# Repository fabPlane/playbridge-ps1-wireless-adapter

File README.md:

# PlayBridge PS1 Wireless Adapter

PlayBridge is an ESP32-based wireless bridge that receives PC controller state
over Wi-Fi and presents it to an original PlayStation through the native PS1
controller protocol.

## Hardware versions

| Version | Design | Status |
| --- | --- | --- |
| `v1.0.0` | Direct PCB-mounted PS1 pin array | Frozen prototype checkpoint under [`versions/v1-pcb-mounted-pin-array/`](versions/v1-pcb-mounted-pin-array/) |
| `v2.0.0` | Modular donor-plug harness through board-mounted 9-contact connectors | Frozen release candidate under [`versions/v2-donor-plug-modular-adapter/`](versions/v2-donor-plug-modular-adapter/) |
| `v2.1.0` | V2.0 baseline plus status LEDs and UART debug access | Release candidate under [`versions/v2.1-status-leds-uart-debug/`](versions/v2.1-status-leds-uart-debug/) |
| `v3.0.0` | Combined PS1 controller and serial-harness evaluation | Frozen development checkpoint under [`versions/v3.0-ps1-serial-harness/`](versions/v3.0-ps1-serial-harness/) |
| `v4.0.0` | New two-layer controller/serial bridge with protected dual-source power | Digitally verified design under [`versions/v4.0-controller-serial-bridge/`](versions/v4.0-controller-serial-bridge/); physical qualification pending |
| `v4.1.0` | V4.0 electrical design with ANTS-compatible enlarged routed vias | Digitally verified fabrication revision under [`versions/v4.1-controller-serial-bridge/`](versions/v4.1-controller-serial-bridge/); physical qualification pending |

Each hardware version is a self-contained FabDesk project under `versions/`.
Open the version directory itself in FabDesk; the repository root is only the
project index plus shared firmware and documentation.

## V4.0.0 status

- Board: 68 × 60 mm, two copper layers.
- J1: PS1 controller harness with open-drain DATA and ACK stages.
- J2: PS1 serial harness on ESP32 UART2.
- Power: protected USB-C and PS1 inputs, TPS2116 source mux, AP63203 buck,
  and AP2112K 3.3 V regulation.
- Programming: CH340C with manual BOOT and RESET switches; automatic DTR/RTS
  behavior is present but is not required for acceptance.
- Indicators: always-on power LED and firmware-controlled status LED.
- Digital checks: ERC, DRC, schematic/PCB parity, BOM/CPL reference parity,
  fabrication archive integrity, and export manifest all pass.
- Manufacturing: bare-board Gerbers and in-house assembly BOM/CPL are present.
- Production remains on hold until the current-limited power, source-switching,
  programming, J1, and J2 bench tests are recorded.

See [`versions/v4.0-controller-serial-bridge/README.md`](versions/v4.0-controller-serial-bridge/README.md)
for the design summary and exact connector/GPIO maps.

## V4.1.0 fabrication revision

V4.1 preserves the V4.0 schematic, component placement, connector mechanics,
GPIO map, and BOM. Its routed through-vias are enlarged to 0.90 mm copper
diameter with 0.40 mm drills to satisfy the ANTS PCB production feedback.
The affected escape routing and manufacturing outputs were regenerated and
pass ERC, DRC, connectivity, drill, and archive-integrity checks. The same
physical bench-test hold still applies.

## V3.0 and V4.0 comparison

| Area | V3.0 | V4.0 | Compatibility / action |
| --- | --- | --- | --- |
| J1/J2 | Hong Cheng C7501856; same signal pinout | Same | Harness-compatible |
| Shells | Isolated | J1→GND pad 4; J2→GND pad 7 | Grounding changed |
| Placement | J1 `(8.025,50.825)`; J2 `(26.025,50.825)` mm | J1 `(14,48.5)`; J2 `(39.2,48.5)` mm | Not mechanically drop-in |
| Controller GPIO | CMD32, CLK33, ATT34, DATA19, ACK21 | CMD19, CLK32, ATT21, DATA33, ACK27/sense34 | Firmware change |
| DATA/ACK | 2N7002 open-drain; no ACK sense | Same drivers plus ACK sense | Firmware change |
| J2 UART | TX17 / RX16 | TX17 / RX16 | Compatible |
| Power | AP63203 + AP2112K + TPS2113A | AP63203 + AP2112K + TPS2116 | Mux changed |
| Protection | USBLC6, SMBJ12A, BAT54 clamps | SMAJ TVS, TPD2EUSB30A, ACK ESD | Prototype-test required |
| LEDs | Red power; yellow-green status GPIO4 | Green power; blue status GPIO25 | GPIO/color change |
| Programming | CH340C; manual BOOT/RESET; DTR/RTS | Same | Auto mode unqualified |
| PCB | 56.295 × 62 mm; 4-layer; 1.2 mm | 68 × 60 mm; 2-layer; 1.6 mm | Size/stackup changed |
| Validation | J1/J2 PoC tested | Digital checks pass; bench pending | First prototype only |

## V2.0.0 historical status

_Board render created with [PCB Fiddle](https://pcbfiddle.com/)._

- Board: 56.295 × 62.000 mm, four copper layers, 1.20 mm thick.
- J1: 9-contact non-USB connector for a genuine PS1 donor-plug harness.
- J2: mechanically identical reserved connector; every contact is intentionally NC.
- J3: USB-C programming/power receptacle on the right edge, facing outward.
- J1 and J2: lower-edge mating mouths face outward and remain registered to the approved Molex footprints.
- Routing: complete; zero unconnected items.
- DRC: zero errors and zero warnings.
- ERC: zero errors and zero warnings.
- Schematic/PCB parity: zero findings.
- FabDesk release gate: PASS.
- PCBA data: 63 fitted references, 32 grouped BOM lines, and four DNP test pads.
- Controller-port bench firmware passed visible original-PS1 system-menu testing over Wi-Fi: all supported digital buttons worked, quick clicks were reliable, and the final check recorded 17,913 complete polls.

The design release is electrically and mechanically validated. Ordering still
requires a final live JLCPCB stock check and review of the uploaded BOM/CPL
rotation previews; see
[`versions/v2-donor-plug-modular-adapter/ordering/DO-NOT-ORDER.md`](versions/v2-donor-plug-modular-adapter/ordering/DO-NOT-ORDER.md).

## Repository layout

- `versions/v1-pcb-mounted-pin-array/` — complete frozen V1 FabDesk project, fit checks, historical renders, and provisional-contact studies.
- `versions/v2-donor-plug-modular-adapter/` — complete V2.0.0 FabDesk project, manufacturing package, reports, tools, references, and accepted renders.
- `versions/v2.1-status-leds-uart-debug/` — complete V2.1.0 FabDesk project, debug interface, manufacturing package, reports, tools, and accepted renders.
- `versions/v3.0-ps1-serial-harness/` — complete V3.0 controller/serial-harness development checkpoint and PoC evidence.
- `versions/v4.0-controller-serial-bridge/` — complete V4.0 FabDesk project, local libraries, validation evidence, renders, and manufacturing package.
- `versions/v4.1-controller-serial-bridge/` — V4.1 ANTS-compatible via revision, regenerated validation evidence, renders, and manufacturing package.
- `firmware/playbridge_wifi_test/` — shared ESP32 Wi-Fi controller firmware and bench instructions.
- `docs/` — shared protocol and modular-interconnect diagrams.

## Opening a hardware project

In FabDesk, select the desired directory under `versions/`, not the repository
root. New hardware work should begin by copying the latest applicable version
to a new version directory so previous releases remain unchanged.

## Important connector warning

J1 and J2 use USB 3 Type-A connector hardware only as inexpensive keyed
9-contact interconnects. They carry native console signals and are **NOT USB**.
Never connect either port to a computer, charger, or ordinary USB peripheral.

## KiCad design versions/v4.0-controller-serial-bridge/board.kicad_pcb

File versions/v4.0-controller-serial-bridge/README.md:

# PlayBridge V4.0 — controller + serial bridge

Status: **digital verification PASS; production HOLD pending physical bench tests**.

V4.0 is the self-contained FabDesk/KiCad project for the 68 × 60 mm,
two-layer PlayBridge board. It combines the PS1 controller interface on J1,
the PS1 serial interface on J2, USB-C programming/power, protected PS1 power,
and automatic source selection.

## Interfaces

- J1: pin 1 NC, 2 CMD, 3 CLK, 4 GND, 5 ATT, 6 DATA, 7 ACK, 8 PS1 power,
  and 9 NC. Both shell/retention pads are GND through pad 4.
- J2: pin 1 TX, 4 RX, and 7 GND; all other signal pins are NC. Both
  shell/retention pads are GND through pad 7.
- J1 and J2 use USB-A connector hardware only as keyed PS1 harness ports.
  They are **NOT USB**.
- The SERVICE / DEBUG holes are GND, UART0 TX, and UART0 RX at 3.2 mm pitch.

The exact firmware GPIO map is in `exports/firmware-handoff.md` and
`exports/firmware-pin-map.h`.

## V3.0 and V4.0 comparison

| Area | V3.0 | V4.0 | Compatibility / action |
| --- | --- | --- | --- |
| J1/J2 | Hong Cheng C7501856; same signal pinout | Same | Harness-compatible |
| Shells | Isolated | J1→GND pad 4; J2→GND pad 7 | Grounding changed |
| Placement | J1 `(8.025,50.825)`; J2 `(26.025,50.825)` mm | J1 `(14,48.5)`; J2 `(39.2,48.5)` mm | Not mechanically drop-in |
| Controller GPIO | CMD32, CLK33, ATT34, DATA19, ACK21 | CMD19, CLK32, ATT21, DATA33, ACK27/sense34 | Firmware change |
| DATA/ACK | 2N7002 open-drain; no ACK sense | Same drivers plus ACK sense | Firmware change |
| J2 UART | TX17 / RX16 | TX17 / RX16 | Compatible |
| Power | AP63203 + AP2112K + TPS2113A | AP63203 + AP2112K + TPS2116 | Mux changed |
| Protection | USBLC6, SMBJ12A, BAT54 clamps | SMAJ TVS, TPD2EUSB30A, ACK ESD | Prototype-test required |
| LEDs | Red power; yellow-green status GPIO4 | Green power; blue status GPIO25 | GPIO/color change |
| Programming | CH340C; manual BOOT/RESET; DTR/RTS | Same | Auto mode unqualified |
| PCB | 56.295 × 62 mm; 4-layer; 1.2 mm | 68 × 60 mm; 2-layer; 1.6 mm | Size/stackup changed |
| Validation | J1/J2 PoC tested | Digital checks pass; bench pending | First prototype only |

## Electrical and mechanical verification evidence

- ERC: 0 errors and 0 warnings.
- DRC: 0 violations, 0 unconnected pads, and 0 schematic-parity issues.
- Connectivity: 53/53 named nets and 227/227 connected nodes match.
- Board: 68 × 60 mm, two copper layers.
- J1/J2 signal pins and retention legs cross the 1.6 mm PCB and protrude
  about 1.2 mm below it for soldering.
- Every fitted footprint has a 3D model; TP1/TP2/TP3 are intentionally DNP.
- Engineering BOM: 80 references. Assembly BOM/CPL: 77 fitted references,
  with an exact reference-set match and no blank LCSC codes.
- The fabrication ZIP contains the complete Gerber and drill set and passes
  archive integrity testing.
- `exports/manifest-sha256.txt` verifies the canonical project, manufacturing
  outputs, accepted renders, and final reports.

## Directory layout

- `board.kicad_*`, `circuit.netlist.json`, and `fabdesk.json` — canonical project.
- `NewPlayBridge.pretty/`, `NewPlayBridge.kicad_sym`, and
  `PlayBridge.3dshapes/` — project-local libraries and models.
- `exports/` — canonical Gerbers, fabrication ZIP, BOM, CPL, positions,
  shopping list, firmware handoff, interchange files, and checksum manifest.
- `ordering/` — convenient vendor-facing copies for bare-board ordering and
  in-house assembly preparation.
- `reports/` — final electrical, mechanical, procurement, and verification evidence.
- `renders/` — generated populated-board, connector, and GLB renders.

Open this version directory itself in FabDesk; do not open the repository root.

## Bench-test hold

No assembled V4 board has been bench-qualified. Complete and record the plan
in `reports/bench-test.md` before production approval. In particular, verify
current-limited USB and PS1 power, TPS2116 source switching and backfeed,
manual programming, J1 controller waveforms, J2 UART operation, and L1
temperature/current margin. Manual BOOT/RESET is the accepted programming path.

See `RELEASE-v4.0.0.md` for the digitally verified design-checkpoint statement.

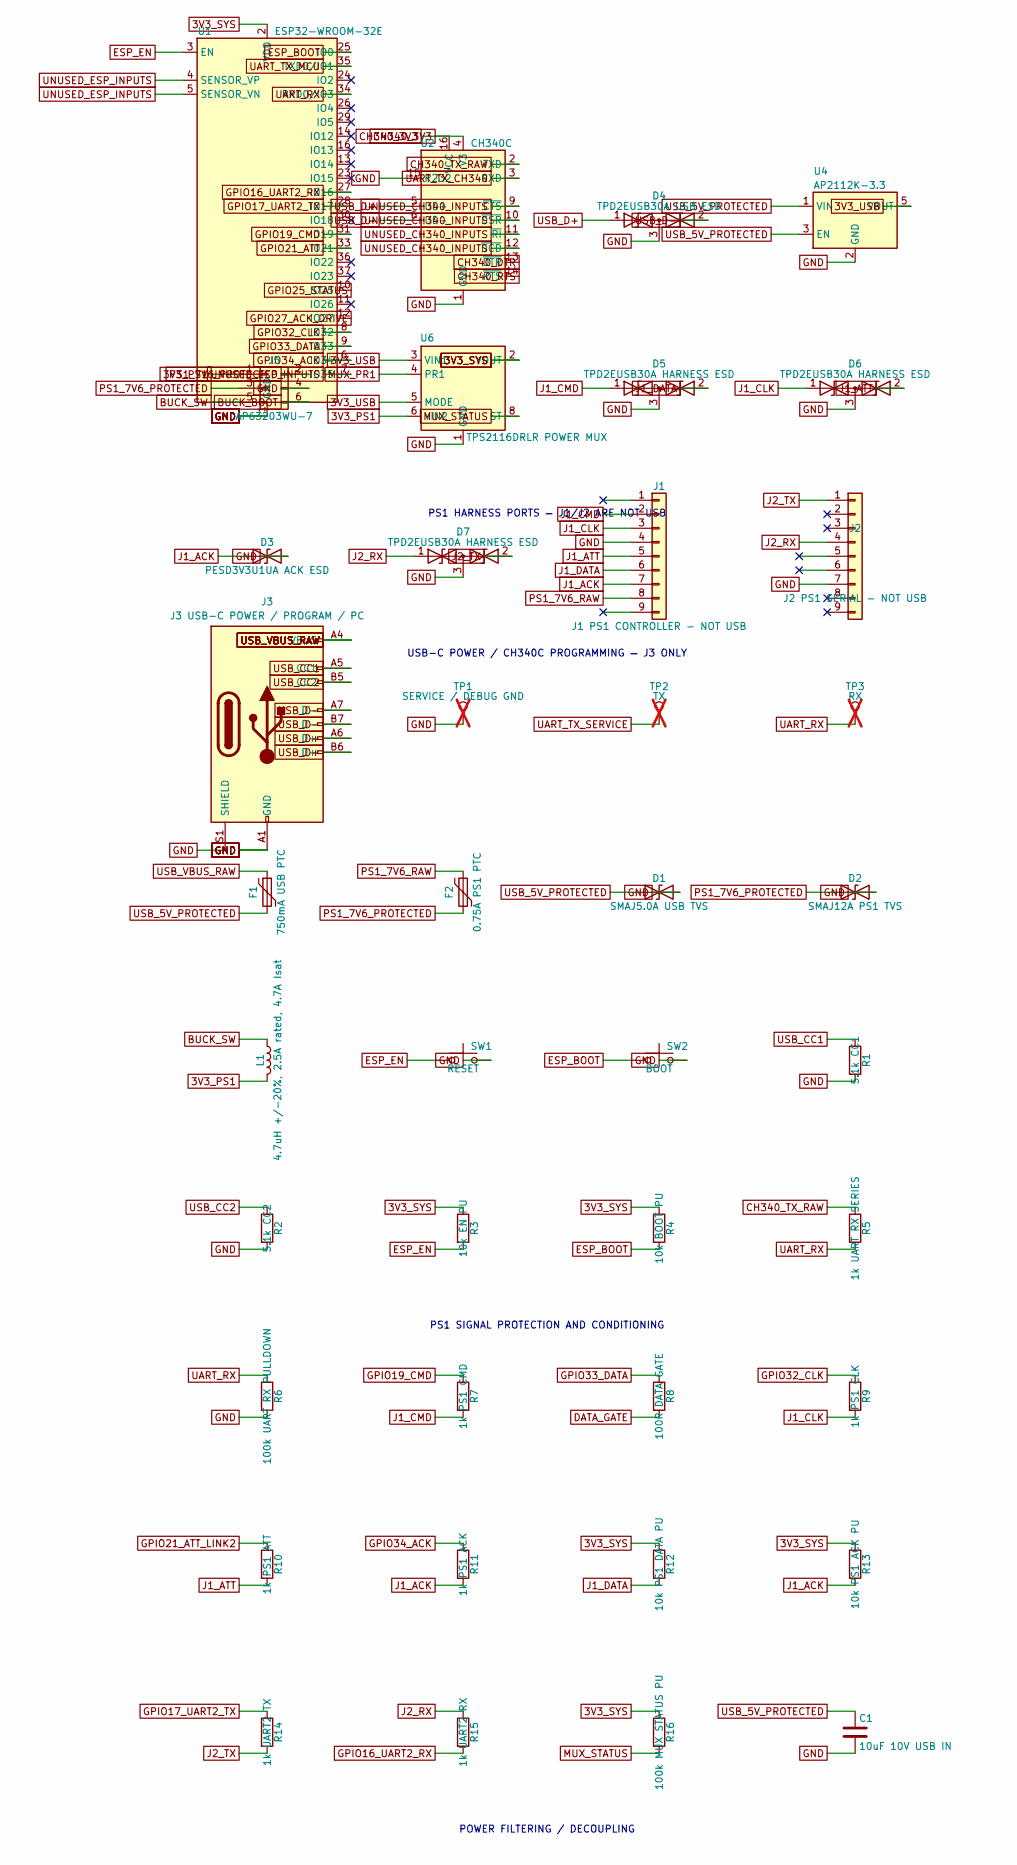
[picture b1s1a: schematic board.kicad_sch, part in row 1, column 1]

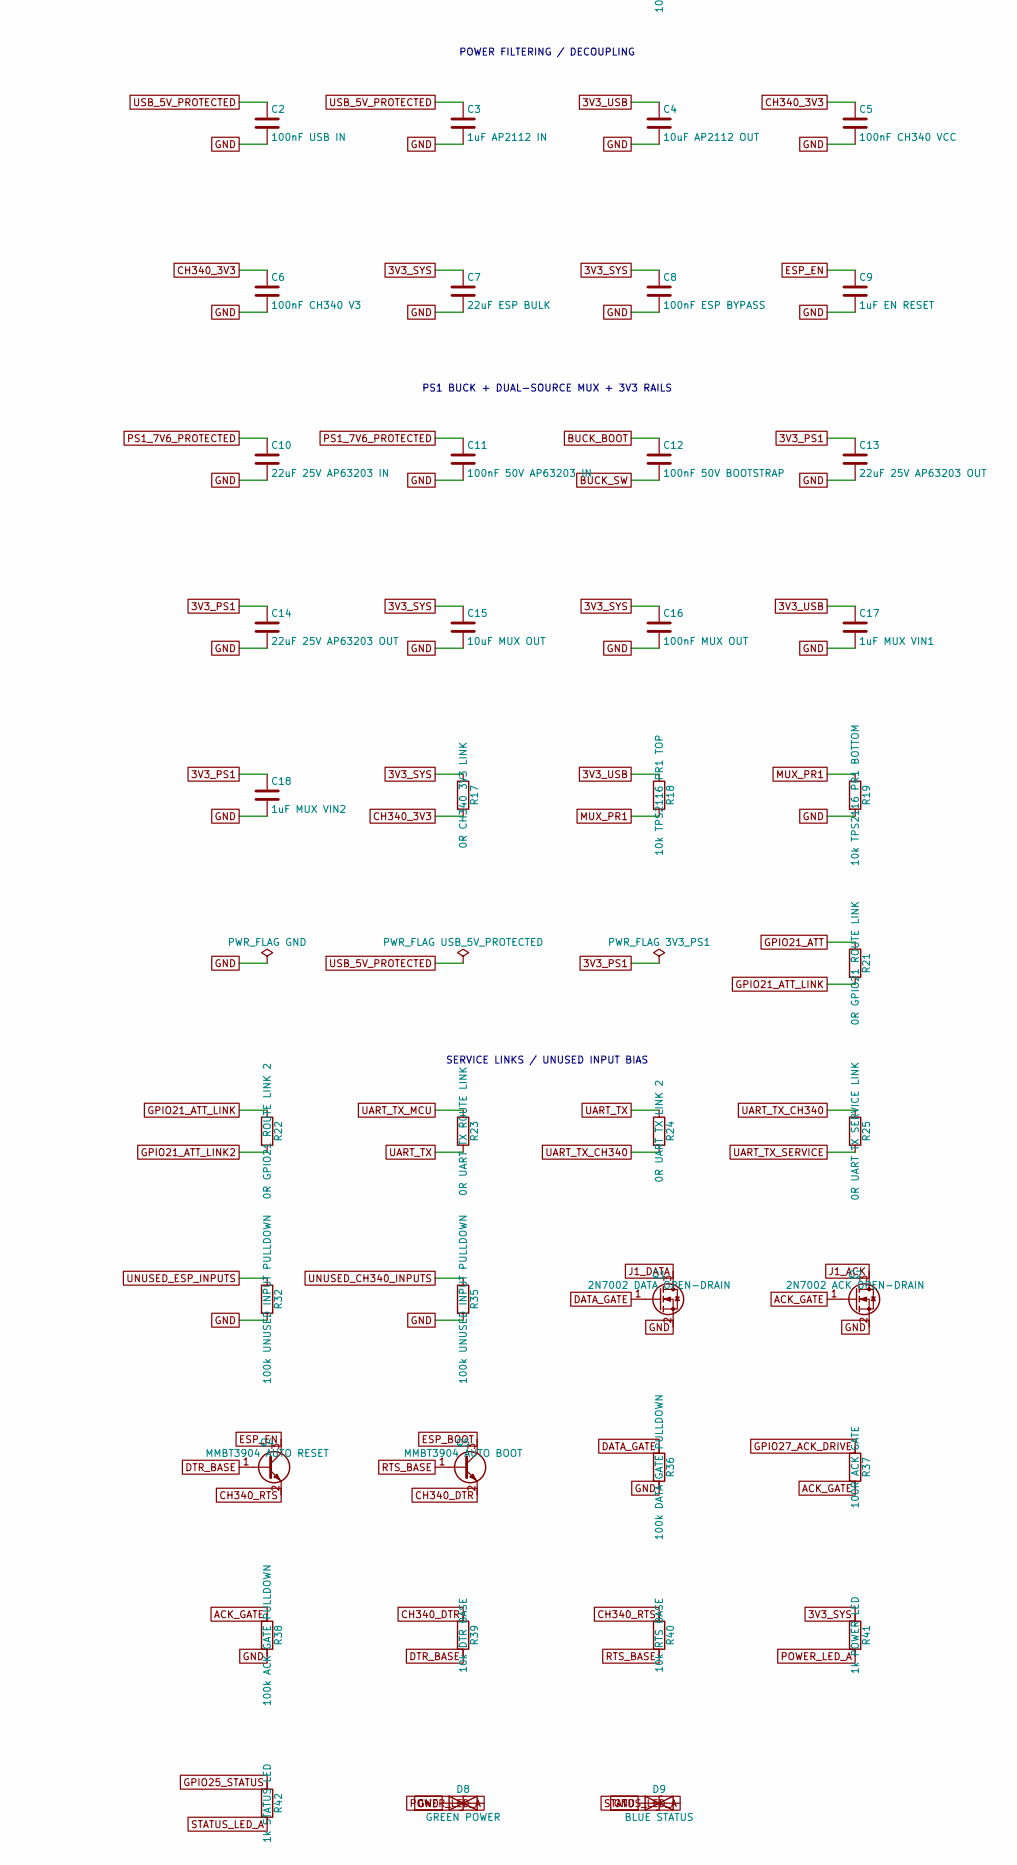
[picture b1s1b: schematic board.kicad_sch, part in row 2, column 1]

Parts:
C1: 10uF 10V USB IN; C_0805_2012Metric; MPN CL21A106KOQNNNE; LCSC C1713
C2: 100nF USB IN; C_0603_1608Metric; MPN CC0603KRX7R9BB104; LCSC C14663
C3: 1uF AP2112 IN; C_0603_1608Metric; MPN CL10A105KA8NNNC; LCSC C5673
C4: 10uF AP2112 OUT; C_0805_2012Metric; MPN CL21A106KOQNNNE; LCSC C1713
C5: 100nF CH340 VCC; C_0603_1608Metric; MPN CC0603KRX7R9BB104; LCSC C14663
C6: 100nF CH340 V3; C_0603_1608Metric; MPN CC0603KRX7R9BB104; LCSC C14663
C7: 22uF ESP BULK; C_0805_2012Metric; MPN CL21A226MQQNNNE; LCSC C5674
C8: 100nF ESP BYPASS; C_0603_1608Metric; MPN CC0603KRX7R9BB104; LCSC C14663
C9: 1uF EN RESET; C_0603_1608Metric; MPN CL10A105KA8NNNC; LCSC C5673
C10: 22uF 25V AP63203 IN; C_1206_3216Metric; MPN CL31A226KAHNNNE; LCSC C12891
C11: 100nF 50V AP63203 IN; C_0603_1608Metric; MPN CC0603KRX7R9BB104; LCSC C14663
C12: 100nF 50V BOOTSTRAP; C_0603_1608Metric; MPN CC0603KRX7R9BB104; LCSC C14663
C13, C14: 22uF 25V AP63203 OUT; C_1206_3216Metric; MPN CL31A226KAHNNNE; LCSC C12891
C15: 10uF MUX OUT; C_0805_2012Metric; MPN CL21A106KOQNNNE; LCSC C1713
C16: 100nF MUX OUT; C_0603_1608Metric; MPN CC0603KRX7R9BB104; LCSC C14663
C17: 1uF MUX VIN1; C_0603_1608Metric; MPN CL10A105KA8NNNC; LCSC C5673
C18: 1uF MUX VIN2; C_0603_1608Metric; MPN CL10A105KA8NNNC; LCSC C5673
D1: SMAJ5.0A USB TVS; D_SMA; MPN SMAJ5.0A; LCSC C140902
D2: SMAJ12A PS1 TVS; D_SMA; MPN SMAJ12A; LCSC C908766
D3: PESD3V3U1UA ACK ESD; D_SOD-323; MPN PESD3V3U1UA,115; LCSC C403915
D4: TPD2EUSB30A USB ESD; Texas_DRT-3; MPN TPD2EUSB30ADRTR-TP; LCSC C2987043
D5, D6, D7: TPD2EUSB30A HARNESS ESD; Texas_DRT-3; MPN TPD2EUSB30ADRTR-TP; LCSC C2987043
D8: GREEN POWER; LED_0603_1608Metric; MPN 19-217/GHC-YR1S2/3T; LCSC C2286
D9: BLUE STATUS; LED_0603_1608Metric; MPN 19-217/BHC-ZL1M2RY/3T; LCSC C2293
F1: 750mA USB PTC; Fuse_1206_3216Metric; MPN BSMD1206-075-30V; LCSC C976305
F2: 0.75A PS1 PTC; Fuse_1206_3216Metric; MPN BSMD1206-075-30V; LCSC C976305
J1: J1 PS1 CONTROLLER - NOT USB; HC-USB3.0-L168-ZP; MPN HC-USB3.0-L168-ZP; LCSC C7501856
J2: J2 PS1 SERIAL - NOT USB; HC-USB3.0-L168-ZP; MPN HC-USB3.0-L168-ZP; LCSC C7501856
J3: J3 USB-C POWER / PROGRAM / PC; USB_C_Receptacle_HRO_TYPE-C-31-M-12_S1; MPN TYPE-C-31-M-12; LCSC C165948
J5: AP63203WU-7; TSOT-23-6; MPN AP63203WU-7; LCSC C780769
L1: 4.7uH +/-20%, 2.5A rated, 4.7A Isat; L_Sunlord_SWPA4020S; MPN CPN4020H4R7MT; LCSC C52741363
Q1: 2N7002 DATA OPEN-DRAIN; SOT-23; MPN 2N7002; LCSC C8545
Q2: 2N7002 ACK OPEN-DRAIN; SOT-23; MPN 2N7002; LCSC C8545
Q4: MMBT3904 AUTO RESET; SOT-23; MPN MMBT3904LT1G; LCSC C81464
Q5: MMBT3904 AUTO BOOT; SOT-23; MPN MMBT3904LT1G; LCSC C81464
R1: 5.1k CC1; R_0402_1005Metric; MPN 0402WGF5101TCE; LCSC C25905
R2: 5.1k CC2; R_0402_1005Metric; MPN 0402WGF5101TCE; LCSC C25905
R3: 10k EN PU; R_0603_1608Metric; MPN 0603WAF1002T5E; LCSC C25804
R4: 10k BOOT PU; R_0603_1608Metric; MPN 0603WAF1002T5E; LCSC C25804
R5: 1k UART RX SERIES; R_0603_1608Metric; MPN 0603WAF1001T5E; LCSC C21190
R6: 100k UART RX PULLDOWN; R_0603_1608Metric; MPN 0603WAF1003T5E; LCSC C25803
R7: 1k PS1 CMD; R_0603_1608Metric; MPN 0603WAF1001T5E; LCSC C21190
R8: 100R DATA GATE; R_0603_1608Metric; MPN 0603WAF1000T5E; LCSC C22775
R9: 1k PS1 CLK; R_0603_1608Metric; MPN 0603WAF1001T5E; LCSC C21190
R10: 1k PS1 ATT; R_0603_1608Metric; MPN 0603WAF1001T5E; LCSC C21190
R11: 1k PS1 ACK; R_0603_1608Metric; MPN 0603WAF1001T5E; LCSC C21190
R12: 10k PS1 DATA PU; R_0603_1608Metric; MPN 0603WAF1002T5E; LCSC C25804
R13: 10k PS1 ACK PU; R_0603_1608Metric; MPN 0603WAF1002T5E; LCSC C25804
R14: 1k UART2 TX; R_0603_1608Metric; MPN 0603WAF1001T5E; LCSC C21190
R15: 1k UART2 RX; R_0603_1608Metric; MPN 0603WAF1001T5E; LCSC C21190
R16: 100k MUX STATUS PU; R_0603_1608Metric; MPN 0603WAF1003T5E; LCSC C25803
R17: 0R CH340 3V3 LINK; R_0402_1005Metric; MPN 0402WGF0000TCE; LCSC C17168
R18: 10k TPS2116 PR1 TOP; R_0603_1608Metric; MPN 0603WAF1002T5E; LCSC C25804
R19: 10k TPS2116 PR1 BOTTOM; R_0603_1608Metric; MPN 0603WAF1002T5E; LCSC C25804
R21: 0R GPIO21 ROUTE LINK; R_0402_1005Metric; MPN 0402WGF0000TCE; LCSC C17168
R22: 0R GPIO21 ROUTE LINK 2; R_0402_1005Metric; MPN 0402WGF0000TCE; LCSC C17168
R23: 0R UART TX ROUTE LINK; R_0402_1005Metric; MPN 0402WGF0000TCE; LCSC C17168
R24: 0R UART TX LINK 2; R_0402_1005Metric; MPN 0402WGF0000TCE; LCSC C17168
R25: 0R UART TX SERVICE LINK; R_0402_1005Metric; MPN 0402WGF0000TCE; LCSC C17168
R32, R35: 100k UNUSED INPUT PULLDOWN; R_0603_1608Metric; MPN 0603WAF1003T5E; LCSC C25803
R36: 100k DATA GATE PULLDOWN; R_0603_1608Metric; MPN 0603WAF1003T5E; LCSC C25803
R37: 100R ACK GATE; R_0603_1608Metric; MPN 0603WAF1000T5E; LCSC C22775
R38: 100k ACK GATE PULLDOWN; R_0603_1608Metric; MPN 0603WAF1003T5E; LCSC C25803
R39: 10k DTR BASE; R_0603_1608Metric; MPN 0603WAF1002T5E; LCSC C25804
R40: 10k RTS BASE; R_0603_1608Metric; MPN 0603WAF1002T5E; LCSC C25804
R41: 1k POWER LED; R_0603_1608Metric; MPN 0603WAF1001T5E; LCSC C21190
R42: 1k STATUS LED; R_0603_1608Metric; MPN 0603WAF1001T5E; LCSC C21190
SW1: RESET; K2-1107ST-A4SW-06; MPN K2-1107ST-A4SW-06; LCSC C2837195
SW2: BOOT; K2-1107ST-A4SW-06; MPN K2-1107ST-A4SW-06; LCSC C2837195
TP1: SERVICE / DEBUG GND; TestPoint_THTPad_D2.0mm_Drill1.0mm; not fitted
TP2: TX; TestPoint_THTPad_D2.0mm_Drill1.0mm; not fitted
TP3: RX; TestPoint_THTPad_D2.0mm_Drill1.0mm; not fitted
U1: ESP32-WROOM-32E; ESP32-WROOM-32E-N4-PROD; MPN ESP32-WROOM-32E-N4; LCSC C701341
U2: CH340C; SOIC-16_3.9x9.9mm_P1.27mm; MPN CH340C; LCSC C84681
U4: AP2112K-3.3; SOT-23-5; MPN AP2112K-3.3TRG1; LCSC C51118
U6: TPS2116DRLR POWER MUX; SOT-583-8; MPN TPS2116DRLR; LCSC C3235557

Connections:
3V3_PS1: C13.1, C14.1, C18.1, J5.1, L1.2, U6.6 (VIN2)
3V3_SYS: C7.1, C8.1, C15.1, C16.1, R3.1, R4.1, R12.1, R13.1, R16.1, R17.1, R41.1, U1.2 (VDD), U6.2 (VOUT), U6.7 (VOUT)
3V3_USB: C4.1, C17.1, R18.1, U4.5 (VOUT), U6.3 (VIN1), U6.5 (MODE)
ACK_GATE: Q2.1 (G), R37.2, R38.1
BUCK_BOOT: C12.1, J5.6
BUCK_SW: C12.2, J5.5, L1.1
CH340_3V3: C5.1, C6.1, R17.2, U2.4 (V3), U2.16 (VCC)
CH340_DTR: Q5.2 (E), R39.1, U2.13 (~DTR)
CH340_RTS: Q4.2 (E), R40.1, U2.14 (~RTS)
CH340_TX_RAW: R5.1, U2.2 (TXD)
DATA_GATE: Q1.1 (G), R8.2, R36.1
DTR_BASE: Q4.1 (B), R39.2
ESP_BOOT: Q5.3 (C), R4.2, SW2.1, U1.25 (IO0)
ESP_EN: C9.1, Q4.3 (C), R3.2, SW1.1, U1.3 (EN)
GND: C1.2, C2.2, C3.2, C4.2, C5.2, C6.2, C7.2, C8.2, C9.2, C10.2, C11.2, C13.2, C14.2, C15.2, C16.2, C17.2, C18.2, D1.2 (A2), D2.2 (A2), D3.2 (A2), D4.3 (common), D5.3 (common), D6.3 (common), D7.3 (common), D8.1 (A1), D9.1 (A1), J1.4, J2.7, J3.A1 (GND), J3.A12 (GND), J3.B1 (GND), J3.B12 (GND), J3.S1 (SHIELD), J5.4, Q1.2 (S), Q2.2 (S), R1.2, R2.2, R6.2, R19.2, R32.2, R35.2, R36.2, R38.2, SW1.2, SW2.2, TP1.1 (1_1), U1.1 (GND), U1.15 (GND), U1.38 (GND), U1.39 (GND), U2.1 (GND), U2.15 (R232), U4.2 (GND), U6.1 (GND)
GPIO16_UART2_RX: R15.2, U1.27 (IO16)
GPIO17_UART2_TX: R14.1, U1.28 (IO17)
GPIO19_CMD: R7.1, U1.31 (IO19)
GPIO21_ATT: R21.1, U1.33 (IO21)
GPIO21_ATT_LINK: R21.2, R22.1
GPIO21_ATT_LINK2: R10.1, R22.2
GPIO25_STATUS: R42.1, U1.10 (IO25)
GPIO27_ACK_DRIVE: R37.1, U1.12 (IO27)
GPIO32_CLK: R9.1, U1.8 (IO32)
GPIO33_DATA: R8.1, U1.9 (IO33)
GPIO34_ACK: R11.1, U1.6 (IO34)
J1_ACK: D3.1 (A1), J1.7, Q2.3 (D), R11.2, R13.2
J1_ATT: D6.2 (A2), J1.5, R10.2
J1_CLK: D6.1 (A1), J1.3, R9.2
J1_CMD: D5.1 (A1), J1.2, R7.2
J1_DATA: D5.2 (A2), J1.6, Q1.3 (D), R12.2
J2_RX: D7.1 (A1), J2.4, R15.1
J2_TX: D7.2 (A2), J2.1, R14.2
MUX_PR1: R18.2, R19.1, U6.4 (PR1)
MUX_STATUS: R16.2, U6.8 (ST)
POWER_LED_A: D8.2 (A2), R41.2
PS1_7V6_PROTECTED: C10.1, C11.1, D2.1 (A1), F2.2, J5.2, J5.3
PS1_7V6_RAW: F2.1, J1.8
RTS_BASE: Q5.1 (B), R40.2
STATUS_LED_A: D9.2 (A2), R42.2
UART_RX: R5.2, R6.1, TP3.1 (1_1), U1.34 (RXD0/IO3)
UART_TX: R23.2, R24.1
UART_TX_CH340: R24.2, R25.1, U2.3 (RXD)
UART_TX_MCU: R23.1, U1.35 (TXD0/IO1)
UART_TX_SERVICE: R25.2, TP2.1 (1_1)
UNUSED_CH340_INPUTS: R35.1, U2.9 (~CTS), U2.10 (~DSR), U2.11 (~RI), U2.12 (~DCD)
UNUSED_ESP_INPUTS: R32.1, U1.4 (SENSOR_VP), U1.5 (SENSOR_VN), U1.7 (IO35)
USB_5V_PROTECTED: C1.1, C2.1, C3.1, D1.1 (A1), F1.2, U4.1 (VIN), U4.3 (EN)
USB_CC1: J3.A5 (CC1), R1.1
USB_CC2: J3.B5 (CC2), R2.1
USB_D+: D4.1 (A1), J3.A6 (D+), J3.B6 (D+), U2.5 (UD+)
USB_D-: D4.2 (A2), J3.A7 (D-), J3.B7 (D-), U2.6 (UD-)
USB_VBUS_RAW: F1.1, J3.A4 (VBUS), J3.A9 (VBUS), J3.B4 (VBUS), J3.B9 (VBUS)

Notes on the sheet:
PS1 HARNESS PORTS — J1/J2 ARE NOT USB
USB-C POWER / CH340C PROGRAMMING — J3 ONLY
POWER FILTERING / DECOUPLING
PS1 BUCK + DUAL-SOURCE MUX + 3V3 RAILS
SERVICE LINKS / UNUSED INPUT BIAS
PS1 SIGNAL PROTECTION AND CONDITIONING

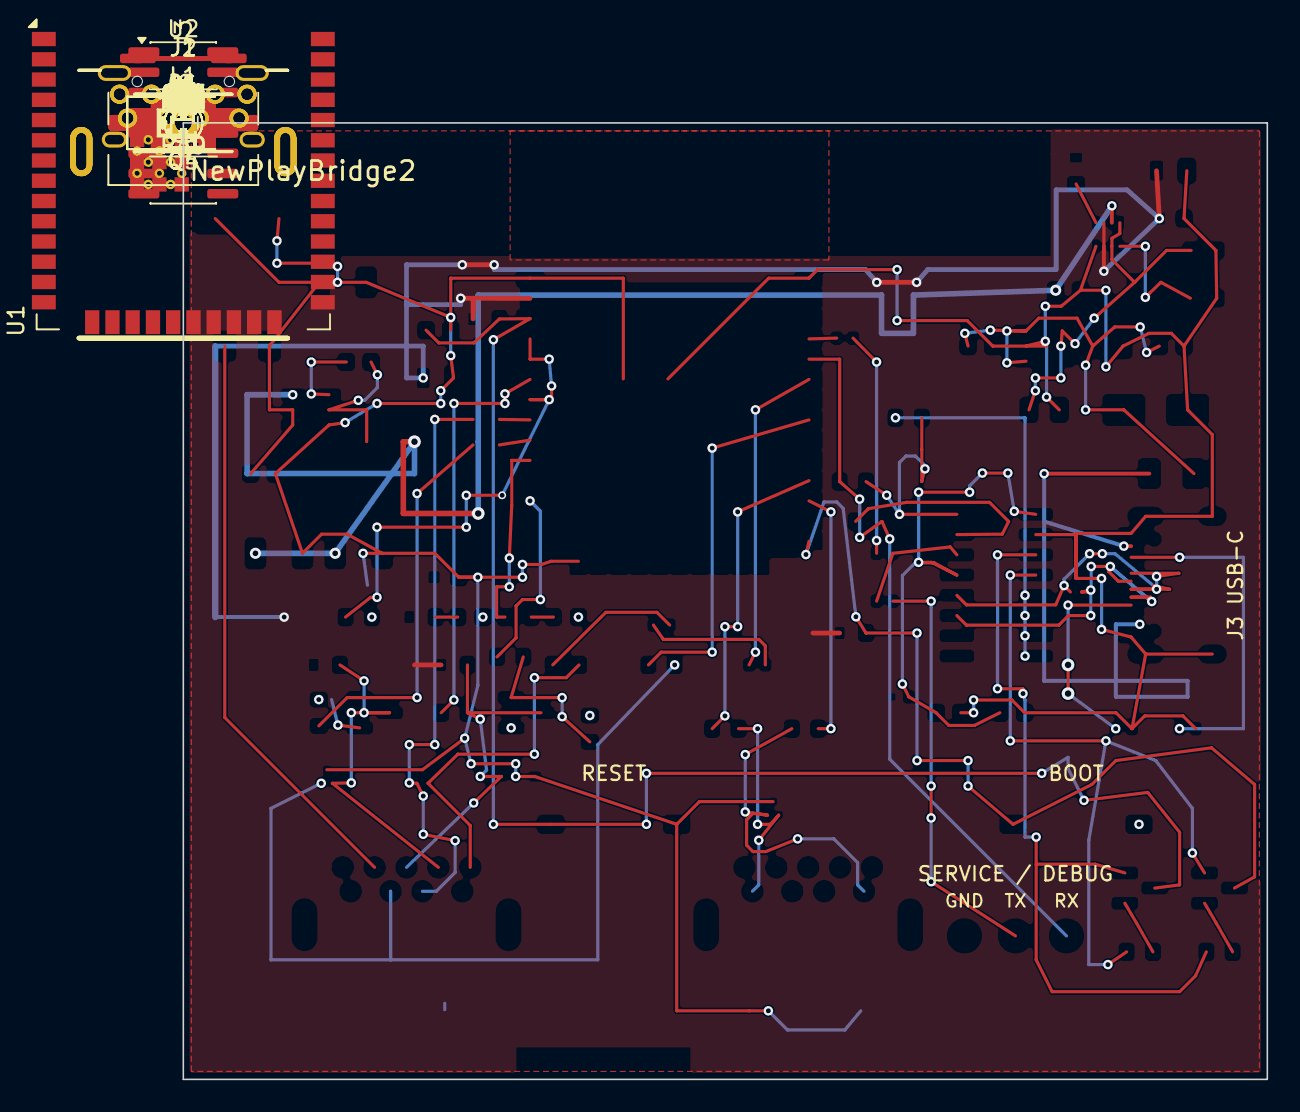
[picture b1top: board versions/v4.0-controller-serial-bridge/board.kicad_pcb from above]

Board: 2 copper layers, 68.0 x 60.0 mm, 80 parts (0 on the bottom side), 53 nets.

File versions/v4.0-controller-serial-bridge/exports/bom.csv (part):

"Designator","Comment","Footprint","Manufacturer","MPN","LCSC","ProcurementNote","Quantity","DNP"
"C1","10uF 10V USB IN","Capacitor_SMD:C_0805_2012Metric","","CL21A106KOQNNNE","C1713","","1",""
"C2","100nF USB IN","Capacitor_SMD:C_0603_1608Metric","","CC0603KRX7R9BB104","C14663","","1",""
"C3","1uF AP2112 IN","Capacitor_SMD:C_0603_1608Metric","","CL10A105KA8NNNC","C5673","","1",""
"C4","10uF AP2112 OUT","Capacitor_SMD:C_0805_2012Metric","","CL21A106KOQNNNE","C1713","","1",""
"C5","100nF CH340 VCC","Capacitor_SMD:C_0603_1608Metric","","CC0603KRX7R9BB104","C14663","","1",""
"C6","100nF CH340 V3","Capacitor_SMD:C_0603_1608Metric","","CC0603KRX7R9BB104","C14663","","1",""
"C7","22uF ESP BULK","Capacitor_SMD:C_0805_2012Metric","","CL21A226MQQNNNE","C5674","","1",""
"C8","100nF ESP BYPASS","Capacitor_SMD:C_0603_1608Metric","","CC0603KRX7R9BB104","C14663","","1",""
"C9","1uF EN RESET","Capacitor_SMD:C_0603_1608Metric","","CL10A105KA8NNNC","C5673","","1",""
"C10","22uF 25V AP63203 IN","Capacitor_SMD:C_1206_3216Metric","","CL31A226KAHNNNE","C12891","","1",""
"C11","100nF 50V AP63203 IN","Capacitor_SMD:C_0603_1608Metric","","CC0603KRX7R9BB104","C14663","","1",""
"C12","100nF 50V BOOTSTRAP","Capacitor_SMD:C_0603_1608Metric","","CC0603KRX7R9BB104","C14663","","1",""
"C13","22uF 25V AP63203 OUT","Capacitor_SMD:C_1206_3216Metric","","CL31A226KAHNNNE","C12891","","1",""
"C14","22uF 25V AP63203 OUT","Capacitor_SMD:C_1206_3216Metric","","CL31A226KAHNNNE","C12891","","1",""
"C15","10uF MUX OUT","Capacitor_SMD:C_0805_2012Metric","","CL21A106KOQNNNE","C1713","","1",""
"C16","100nF MUX OUT","Capacitor_SMD:C_0603_1608Metric","","CC0603KRX7R9BB104","C14663","","1",""
"C17","1uF MUX VIN1","Capacitor_SMD:C_0603_1608Metric","","CL10A105KA8NNNC","C5673","","1",""
"C18","1uF MUX VIN2","Capacitor_SMD:C_0603_1608Metric","","CL10A105KA8NNNC","C5673","","1",""
"D1","SMAJ5.0A USB TVS","Diode_SMD:D_SMA","LRC","SMAJ5.0A","C140902","","1",""
"D2","SMAJ12A PS1 TVS","Diode_SMD:D_SMA","GOODWORK","SMAJ12A","C908766","","1",""
"D3","PESD3V3U1UA ACK ESD","Diode_SMD:D_SOD-323","Nexperia","PESD3V3U1UA,115","C403915","","1",""
"D4","TPD2EUSB30A USB ESD","Package_TO_SOT_SMD:Texas_DRT-3","TECH PUBLIC","TPD2EUSB30ADRTR-TP","C2987043","","1",""
"D5","TPD2EUSB30A HARNESS ESD","Package_TO_SOT_SMD:Texas_DRT-3","TECH PUBLIC","TPD2EUSB30ADRTR-TP","C2987043","","1",""
"D6","TPD2EUSB30A HARNESS ESD","Package_TO_SOT_SMD:Texas_DRT-3","TECH PUBLIC","TPD2EUSB30ADRTR-TP","C2987043","","1",""
"D7","TPD2EUSB30A HARNESS ESD","Package_TO_SOT_SMD:Texas_DRT-3","TECH PUBLIC","TPD2EUSB30ADRTR-TP","C2987043","","1",""
"D8","GREEN POWER","LED_SMD:LED_0603_1608Metric","","19-217/GHC-YR1S2/6T","C2986059","","1",""
"D9","BLUE STATUS","LED_SMD:LED_0603_1608Metric","","19-217/BHC-ZL1M2RY/6T","C2986058","","1",""
"F1","750mA USB PTC","Fuse:Fuse_1206_3216Metric","BHFUSE","BSMD1206-075-30V","C976305","","1",""
"F2","0.75A PS1 PTC","Fuse:Fuse_1206_3216Metric","BHFUSE","BSMD1206-075-30V","C976305","","1",""
"J1","J1 PS1 CONTROLLER - NOT USB","Connector_USB:HC-USB3.0-L168-ZP","Hong Cheng","HC-USB3.0-L168-ZP","C7501856","","1",""
"J2","J2 PS1 SERIAL - NOT USB","Connector_USB:HC-USB3.0-L168-ZP","Hong Cheng","HC-USB3.0-L168-ZP","C7501856","","1",""
"J3","J3 USB-C POWER / PROGRAM / PC","Connector_USB:USB_C_Receptacle_HRO_TYPE-C-31-M-12_S1","Korean Hroparts","TYPE-C-31-M-12","C165948","","1",""
"J5","AP63203WU-7","Package_TO_SOT_SMD:TSOT-23-6","Diodes Incorporated","AP63203WU-7","C780769","","1",""
"L1","4.7uH +/-20%, 2.5A rated, 4.7A Isat","Inductor_SMD:L_Sunlord_SWPA4020S","Magnetsyc","CPN4020H4R7MT","C52741363","4.7uH +/-20%; 2.5A rated; 4.7A Isat; SMD 4x4mm","1",""
"Q1","2N7002 DATA OPEN-DRAIN","Package_TO_SOT_SMD:SOT-23","Jiangsu Changjing Electronics","2N7002","C8545","","1",""
"Q2","2N7002 ACK OPEN-DRAIN","Package_TO_SOT_SMD:SOT-23","Jiangsu Changjing Electronics","2N7002","C8545","","1",""
"Q4","MMBT3904 AUTO RESET","Package_TO_SOT_SMD:SOT-23","onsemi","MMBT3904LT1G","C81464","","1",""
"Q5","MMBT3904 AUTO BOOT","Package_TO_SOT_SMD:SOT-23","onsemi","MMBT3904LT1G","C81464","","1",""
"R1","5.1k CC1","Resistor_SMD:R_0402_1005Metric","","0402WGF5101TCE","C25905","","1",""
"R2","5.1k CC2","Resistor_SMD:R_0402_1005Metric","","0402WGF5101TCE","C25905","","1",""
"R3","10k EN PU","Resistor_SMD:R_0603_1608Metric","","0603WAF1002T5E","C25804","","1",""
"R4","10k BOOT PU","Resistor_SMD:R_0603_1608Metric","","0603WAF1002T5E","C25804","","1",""
"R5","1k UART RX SERIES","Resistor_SMD:R_0603_1608Metric","","0603WAF1001T5E","C21190","","1",""
"R6","100k UART RX PULLDOWN","Resistor_SMD:R_0603_1608Metric","","0603WAF1003T5E","C25803","","1",""
"R7","1k PS1 CMD","Resistor_SMD:R_0603_1608Metric","","0603WAF1001T5E","C21190","","1",""
"R8","100R DATA GATE","Resistor_SMD:R_0603_1608Metric","","0603WAF1000T5E","C22775","","1",""
"R9","1k PS1 CLK","Resistor_SMD:R_0603_1608Metric","","0603WAF1001T5E","C21190","","1",""
"R10","1k PS1 ATT","Resistor_SMD:R_0603_1608Metric","","0603WAF1001T5E","C21190","","1",""
"R11","1k PS1 ACK","Resistor_SMD:R_0603_1608Metric","","0603WAF1001T5E","C21190","","1",""
"R12","10k PS1 DATA PU","Resistor_SMD:R_0603_1608Metric","","0603WAF1002T5E","C25804","","1",""
"R13","10k PS1 ACK PU","Resistor_SMD:R_0603_1608Metric","","0603WAF1002T5E","C25804","","1",""
"R14","1k UART2 TX","Resistor_SMD:R_0603_1608Metric","","0603WAF1001T5E","C21190","","1",""
"R15","1k UART2 RX","Resistor_SMD:R_0603_1608Metric","","0603WAF1001T5E","C21190","","1",""
"R16","100k MUX STATUS PU","Resistor_SMD:R_0603_1608Metric","","0603WAF1003T5E","C25803","","1",""
"R17","0R CH340 3V3 LINK","Resistor_SMD:R_0402_1005Metric","","0402WGF0000TCE","C17168","","1",""
"R18","10k TPS2116 PR1 TOP","Resistor_SMD:R_0603_1608Metric","","0603WAF1002T5E","C25804","","1",""
"R19","10k TPS2116 PR1 BOTTOM","Resistor_SMD:R_0603_1608Metric","","0603WAF1002T5E","C25804","","1",""
"R21","0R GPIO21 ROUTE LINK","Resistor_SMD:R_0402_1005Metric","","0402WGF0000TCE","C17168","","1",""
"R22","0R GPIO21 ROUTE LINK 2","Resistor_SMD:R_0402_1005Metric","","0402WGF0000TCE","C17168","","1",""
"R23","0R UART TX ROUTE LINK","Resistor_SMD:R_0402_1005Metric","","0402WGF0000TCE","C17168","","1",""
"R24","0R UART TX LINK 2","Resistor_SMD:R_0402_1005Metric","","0402WGF0000TCE","C17168","","1",""
"R25","0R UART TX SERVICE LINK","Resistor_SMD:R_0402_1005Metric","","0402WGF0000TCE","C17168","","1",""
"R32","100k UNUSED INPUT PULLDOWN","Resistor_SMD:R_0603_1608Metric","","0603WAF1003T5E","C25803","","1",""
"R35","100k UNUSED INPUT PULLDOWN","Resistor_SMD:R_0603_1608Metric","","0603WAF1003T5E","C25803","","1",""
"R36","100k DATA GATE PULLDOWN","Resistor_SMD:R_0603_1608Metric","","0603WAF1003T5E","C25803","","1",""
"R37","100R ACK GATE","Resistor_SMD:R_0603_1608Metric","","0603WAF1000T5E","C22775","","1",""
"R38","100k ACK GATE PULLDOWN","Resistor_SMD:R_0603_1608Metric","","0603WAF1003T5E","C25803","","1",""
"R39","10k DTR BASE","Resistor_SMD:R_0603_1608Metric","","0603WAF1002T5E","C25804","","1",""
"R40","10k RTS BASE","Resistor_SMD:R_0603_1608Metric","","0603WAF1002T5E","C25804","","1",""
"R41","1k POWER LED","Resistor_SMD:R_0603_1608Metric","","0603WAF1001T5E","C21190","","1",""
"R42","1k STATUS LED","Resistor_SMD:R_0603_1608Metric","","0603WAF1001T5E","C21190","","1",""
"SW1","RESET","Button_Switch_SMD:K2-1107ST-A4SW-06","Korean Hroparts","K2-1107ST-A4SW-06","C2837195","","1",""
"SW2","BOOT","Button_Switch_SMD:K2-1107ST-A4SW-06","Korean Hroparts","K2-1107ST-A4SW-06","C2837195","","1",""
"TP1","SERVICE / DEBUG GND","TestPoint:TestPoint_THTPad_D2.0mm_Drill1.0mm","","","","","1","DNP"
"TP2","TX","TestPoint:TestPoint_THTPad_D2.0mm_Drill1.0mm","","","","","1","DNP"
"TP3","RX","TestPoint:TestPoint_THTPad_D2.0mm_Drill1.0mm","","","","","1","DNP"
"U1","ESP32-WROOM-32E","RF_Module:ESP32-WROOM-32E-N4-PROD","Espressif Systems","ESP32-WROOM-32E-N4","C701341","","1",""
"U2","CH340C","Package_SO:SOIC-16_3.9x9.9mm_P1.27mm","WCH","CH340C","C84681","","1",""
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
